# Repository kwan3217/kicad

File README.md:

# kicad
KiCad versions of my circuits

Many of my boards have the Open Source Hardware logo on them. Using this logo
requires having an open source license and publishing the source. In order to
support this, I have the URL of this repository engraved onto the boards themselves.

I have made a release for the Wearable Pocketometer boards, and intend to make a release
each time I have a board made.

All boards which have been released since September 2020 have enough information
to construct a bill of materials. This is in the form of Digikey part numbers attached
to each part in the KiCad .sch files.

Featured projects:

* Wearable Pocketometer -- IMU/GPS recording device designed to be worn by a roller-coaster passenger. 
It has a component that goes on your shoulder or hat, one in your pocket, and one in your shoe.

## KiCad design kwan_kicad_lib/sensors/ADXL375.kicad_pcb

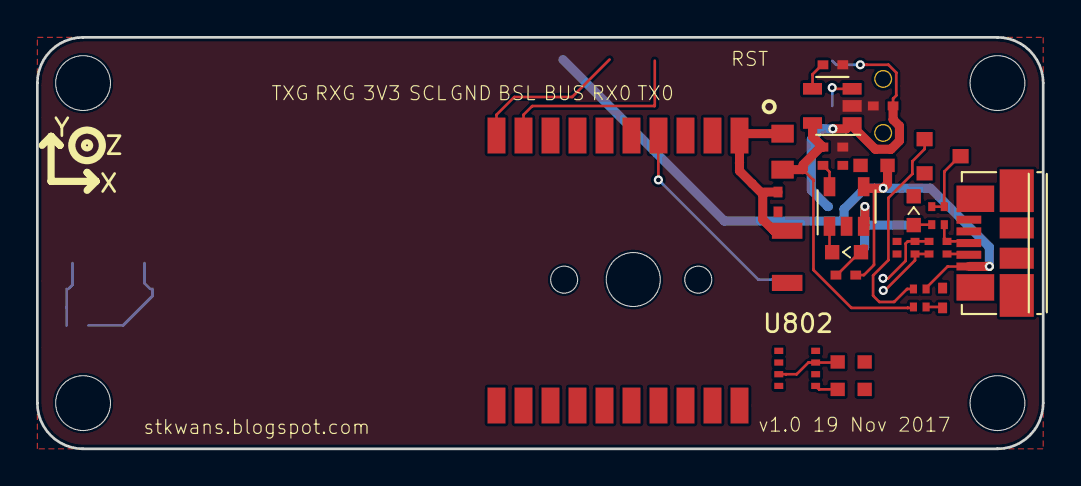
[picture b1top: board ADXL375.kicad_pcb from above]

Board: 2 copper layers, 55.9 x 22.9 mm, 39 parts (0 on the bottom side), 25 nets.

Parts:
B504: Coin_Cell; CR1220-2
C401, C405, C501, C714: 100nF; SMD_0402
C406, C704: 1uF; SMD_0402
C503: 10uF; SMD_1206
C623: 22pF; R_Array_Convex_2x0402
C715: 4.7nF; SMD_0402
C802, C803: 4.7uF; SMD_0603
C806, C808: 100nF; SMD_0603
D650: BLUE; D_0603
D801: YELLOW; D_0603
D802: DCC; SOT-23
J601: USB_MICROB; USB_Micro-B_Molex_47346-0001
J801: JST 2mm; SPARKFUN_JST_POWER
JP1, JP2, JP4, JP5: STAND-OFFTIGHT; STAND-OFF-TIGHT
L501: Ferrite; SMD_0805
Q650: PMOS; SOT-23
R406: 100; SMD_0402
R611: 22k; SMD_0402
R623: 33; R_Array_Convex_2x0402
R650: 1.5k; R_Array_Convex_2x0402
R651: 10k; R_Array_Convex_2x0402
R801: 10k; SMD_0402
R804: 1.5k; SMD_0402
S701: SPDT; SWITCH_DPDT_AZY0202
U401: ADXL375
U501: FGPMMOPA6H
U599: FGPMMOPA6H; Axis
U701: 3.3V; SOT-23-5
U801: MCP73831; SOT-23-5
U802: BME280

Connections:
/CONNECT: Q650.1, R651.4
/CONN_D+: J601.3, R623.4, R650.4
/CONN_D-: J601.2, R623.3
/D+: C623.2, R623.1
/D-: C623.1, R623.2
/GND: B504.-, C401.2, C405.2, C406.2, C501.1, C503.1, C623.3, C623.4, C802.2, C803.2, C806.1, C808.1, D650.1, J601.5, J601.6, J801.-, R611.1, R801.1, U401.2, U401.4, U401.5, U401.12, U501.3, U501.8, U501.12, U501.19, U801.2, U802.1, U802.5, U802.7
/ON: R611.2, R651.2
/PROG: R801.2, U801.5
/Regulator/BYP: C714.1, U701.4
/Regulator/PWR_EN: S701.2, U701.3
/SCL: U401.14, U802.4
/SDA: U401.13, U802.3
/STAT+: D801.2, R804.2
/STAT-: D801.1, U801.1
/USB_LIGHT+: Q650.3, R650.1, R650.2
/USB_LIGHT-: D650.2, R650.3
/VBACKUP: B504.+, U501.4
/VBUS: C802.1, D802.1, J601.1, R651.3, R804.1, U801.4
/VCC: C401.1, C806.2, C808.2, R406.1, U401.1, U401.7, U802.2, U802.6, U802.8
/VGPS: C501.2, C503.2, L501.2, U501.1
/VLIPO: C803.1, D802.2, J801.+, U801.3
/VRAW: C704.1, D802.3, S701.1, U701.1
/VS: C405.1, C406.1, R406.2, U401.6
GND: C704.2, C714.2, C715.2, S701.3, U701.2
VCC: C715.1, L501.1, R651.1, U701.5

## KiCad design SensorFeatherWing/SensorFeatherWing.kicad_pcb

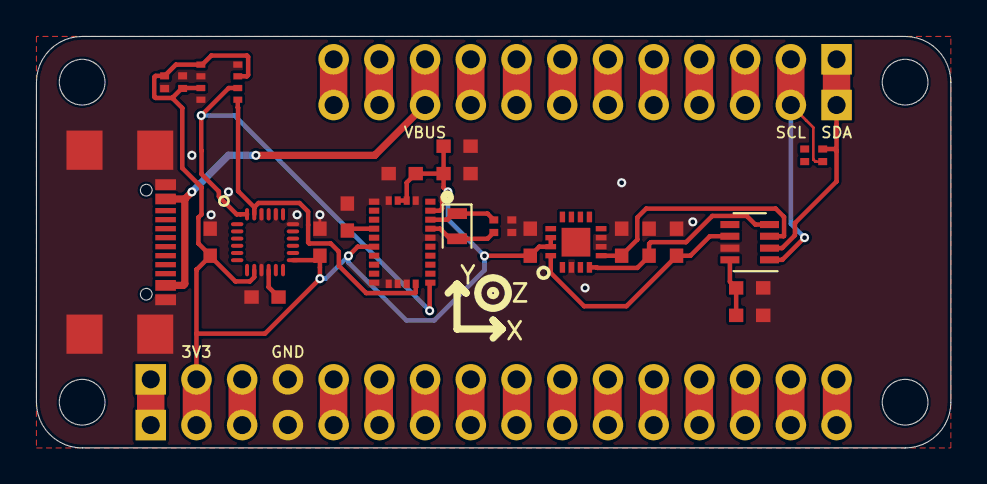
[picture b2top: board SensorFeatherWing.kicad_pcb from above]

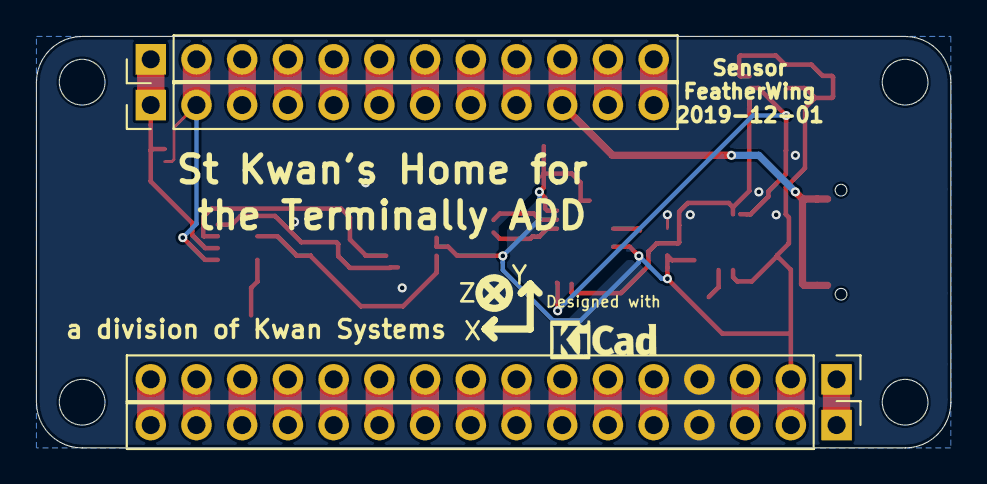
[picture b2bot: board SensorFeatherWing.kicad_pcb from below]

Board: 2 copper layers, 50.8 x 22.9 mm, 32 parts (4 on the bottom side), 35 nets.

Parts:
C208, C210, C213, C401, C402, C403, C607, C703, C709: 100nF; SMD_0603
C306: 100nF; R_Array_Convex_2x0402
C505: 4.7uF; SMD_0603
C608: 10uF; SMD_0603
C725: 120nF; SMD_0603
C726: 22pF; R_Array_Convex_2x0402
C728: 6.8nF; SMD_0603
J101, J102, J105, J106: STANDOFF; STANDOFF_FEATHER
J103, J107: Conn_01x16_Male; PinHeader_1x16_P2.54mm_Vertical
J104, J108: Conn_01x12_Male; PinHeader_1x12_P2.54mm_Vertical
J109: USB_C_Receptacle_USB2.0; USB4110
R101: 10k; R_Array_Convex_2x0402
U201: MPU9250; QFN24_PAD
U301: BME280
U501: MPU9250; Axis
U501#2: ADXL377
U601: AD7991; SOT-23-8
U701: BNO055
Y701: 32kiHz; Crystal_SMD_2012-2Pin_2.0x1.2mm

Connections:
+3V3: C208.2, C213.2, C306.1, C306.3, C505.1, C607.1, C608.1, C703.2, C725.1, C728.1, J103.2, J107.2, R101.1, R101.2, U201.8, U201.13, U301.2, U301.6, U301.8, U501#2.14, U501#2.15, U601.8, U701.3, U701.4, U701.11, U701.28
/BNO055/CAP: C709.1, U701.9
/BNO055/XIN32: C726.1, U701.27, Y701.1
/BNO055/XOUT32: C726.2, U701.26, Y701.2
/HighAcc/XACC: C403.2, U501#2.5, U601.3
/HighAcc/YACC: C402.2, U501#2.4, U601.4
/HighAcc/ZACC: C401.2, U501#2.16, U601.6
/MPU9250/REGOUT: C210.2, U201.10
/SCL: J104.2, J108.2, R101.3, U201.23, U301.4, U601.1, U701.19
/SDA: J104.1, J108.1, R101.4, U201.24, U301.3, U601.2, U701.20
GND: C208.1, C210.1, C213.1, C306.2, C306.4, C401.1, C402.1, C403.1, C505.2, C607.2, C608.2, C703.1, C709.2, C725.2, C726.3, C726.4, C728.2, J103.4, J107.4, J109.A1, J109.A12, J109.B1, J109.B12, J109.S1, U201.9, U201.18, U201.20, U201.22, U301.1, U301.5, U301.7, U501#2.2, U501#2.6, U501#2.7, U601.7, U701.2, U701.5, U701.6, U701.15, U701.16, U701.17, U701.18, U701.25
unnamed: J103.1, J107.1
unnamed: J103.3, J107.3
unnamed: J103.5, J107.5
unnamed: J103.6, J107.6
unnamed: J103.7, J107.7
unnamed: J103.8, J107.8
unnamed: J103.9, J107.9
unnamed: J103.10, J107.10
unnamed: J103.11, J107.11
unnamed: J103.12, J107.12
unnamed: J103.13, J107.13
unnamed: J103.14, J107.14
unnamed: J103.15, J107.15
unnamed: J103.16, J107.16
unnamed: J104.3, J108.3
unnamed: J104.4, J108.4
unnamed: J104.5, J108.5
unnamed: J104.6, J108.6
unnamed: J104.7, J108.7
unnamed: J104.8, J108.8
unnamed: J104.9, J108.9
unnamed: J104.11, J108.11
unnamed: J104.12, J108.12
VBUS: J104.10, J108.10, J109.A4, J109.A9, J109.B4, J109.B9

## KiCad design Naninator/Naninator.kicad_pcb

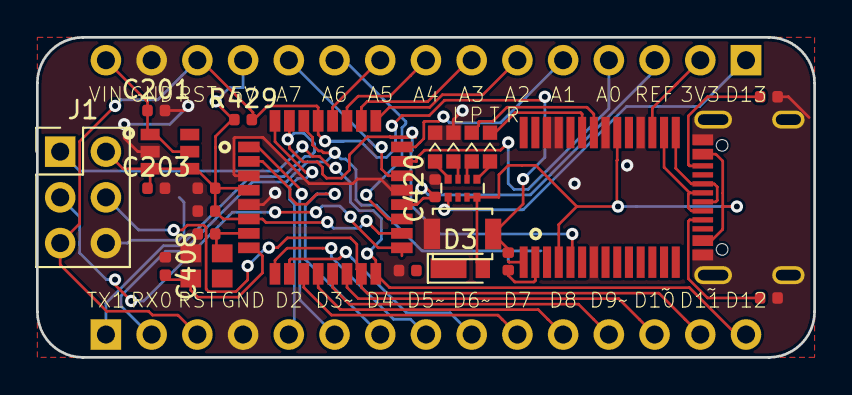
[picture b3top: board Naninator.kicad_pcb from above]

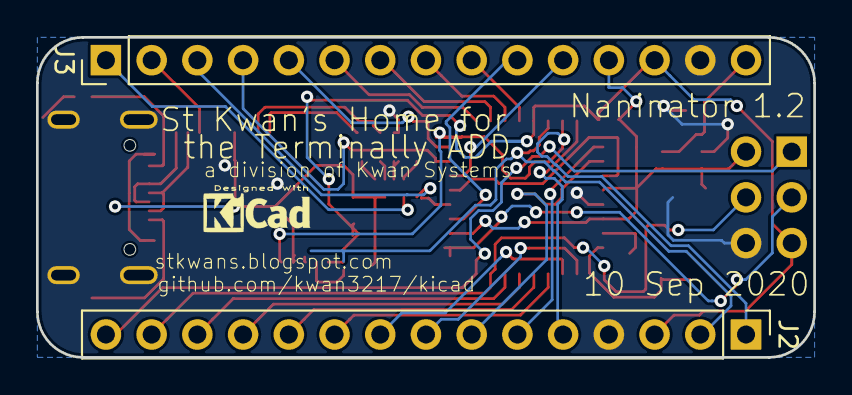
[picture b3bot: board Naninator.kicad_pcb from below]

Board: 2 copper layers, 43.2 x 17.8 mm, 29 parts (4 on the bottom side), 42 nets.

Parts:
C201: 1uF; C_0402_1005Metric
C203: 4.7uF; C_0402_1005Metric
C302, C404, C406, C418, C420: 100nF; C_0402_1005Metric
C407, C408: 22pF; C_0402_1005Metric
D3: MSSP12L; D_TUMD2
D322: BLUE; D_0603
D323: RED; D_0603
D401: GREEN; D_0603
D402: YELLOW; D_0603
G101: Designed With; Symbol_KiCAD-Logo_CopperAndSilkScreenTop_small
G102: KwanSystems; StKwansSoldermask
J1: CONN_02X03; PinHeader_2x03_P2.54mm_Vertical
J2, J3: CONN_01X15; PinHeader_1x15_P2.54mm_Vertical
J401: USB_C_Receptacle_USB2.0; GCTUSBTypeC_PTH
R201: 680; R_Array_Convex_4x0402
R401, R402: 5.1k; R_0402_1005Metric
R429: 10k; R_0402_1005Metric
S429: SW_SPST; SW_SPST_B3U-1000P
U201: MAX8881 5V; SOT-23-6
U301: FT232RL; SSOP-28_5.3x10.2mm_Pitch0.65mm
U401: ATMEGA328P-AU; LQFP-32_7x7mm_Pitch0.8mm
Y407: 16MHz; Crystal_SMD_2520-4pin_2.5x2.0mm

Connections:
+3V3: J3.2, U301.17
/A0: J3.4, U401.23
/A1: J3.5, U401.24
/A2: J3.6, U401.25
/A3: J3.7, U401.26
/A4: J3.8, U401.27
/A5: J3.9, U401.28
/A6: J3.10, U401.19
/A7: J3.11, U401.22
/AREF: C420.1, J3.3, U401.20
/ATmega/XTAL1: C407.2, U401.7, Y407.1
/ATmega/XTAL2: C408.2, U401.8, Y407.3
/D0/RX: J2.2, U301.1, U401.30
/D1/TX: J2.1, U301.5, U401.31
/D2: J2.5, U401.32
/D3: J2.6, U401.1
/D4: J2.7, U401.2
/D5: J2.8, U401.9
/D6: J2.9, U401.10
/D7: J2.10, U401.11
/D8: J2.11, U401.12
/D9: J2.12, U401.13
/D10: J2.13, U401.14
/D11: J1.4, J2.14, U401.15
/D12: J1.1, J2.15, U401.16
/D13: J1.3, J3.1, R201.5, U401.17
/D13-: D402.2, R201.4
/PWR_LED-: D401.2, R201.3
/USB Serial/D+: J401.A6, J401.B6, U301.15
/USB Serial/D-: J401.A7, J401.B7, U301.16
/USB Serial/DTR: C302.1, U301.2
/USB Serial/RX_LED+: D323.2, R201.1
/USB Serial/RX_LED-: D323.1, U301.23
/USB Serial/TX_LED+: D322.2, R201.2
/USB Serial/TX_LED-: D322.1, U301.22
/USB Serial/USB-C Connector/CC1: J401.A5, R401.1
/USB Serial/USB-C Connector/CC2: J401.B5, R402.1
/VBUS: D3.2, J401.A4, J401.A9, J401.B4, J401.B9, R201.7, R201.8, U301.4, U301.20
/~RESET: C302.2, J1.5, J2.3, J3.13, R429.2, S429.1, U401.29
GND: C201.2, C203.2, C404.2, C406.2, C407.1, C408.1, C418.2, C420.2, D401.1, D402.1, J1.6, J2.4, J3.14, J401.A1, J401.A12, J401.B1, J401.B12, J401.S1, R401.2, R402.2, S429.2, U201.2, U301.7, U301.18, U301.21, U301.25, U301.26, U401.3, U401.5, U401.21, Y407.2
HT: C201.1, J3.15, U201.1, U201.5
VCC: C203.1, C404.1, C406.1, C418.1, D3.1, J1.2, J3.12, R201.6, R429.1, U201.3, U201.4, U401.4, U401.6, U401.18

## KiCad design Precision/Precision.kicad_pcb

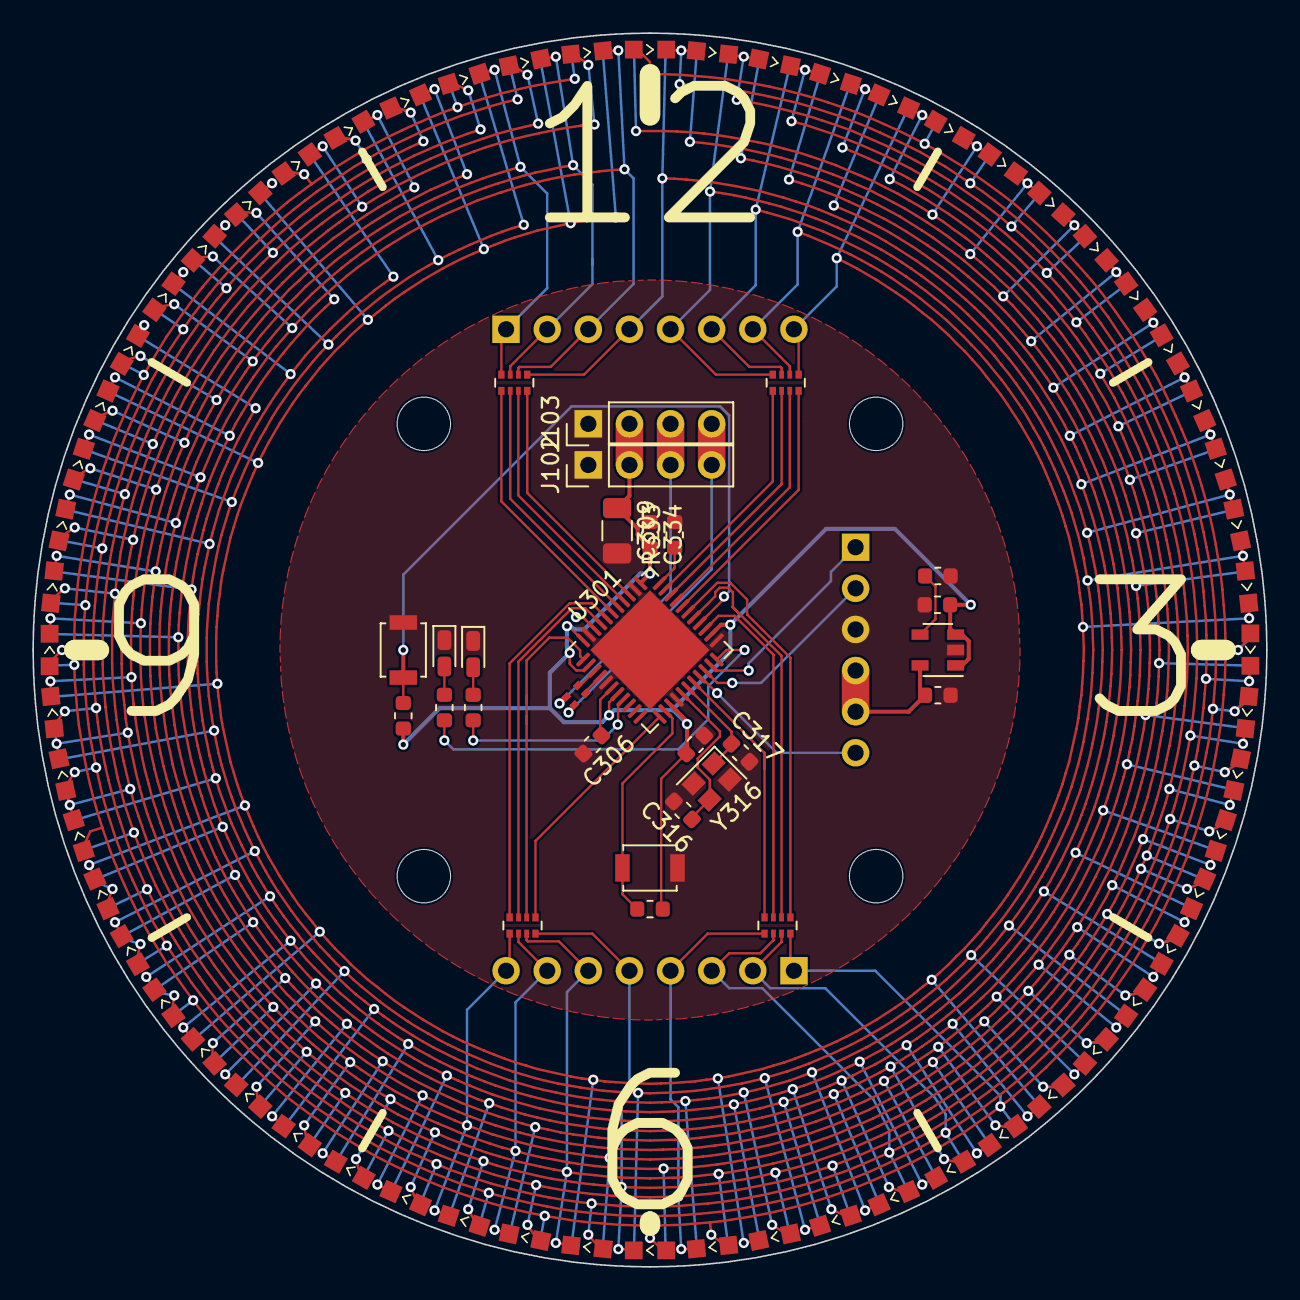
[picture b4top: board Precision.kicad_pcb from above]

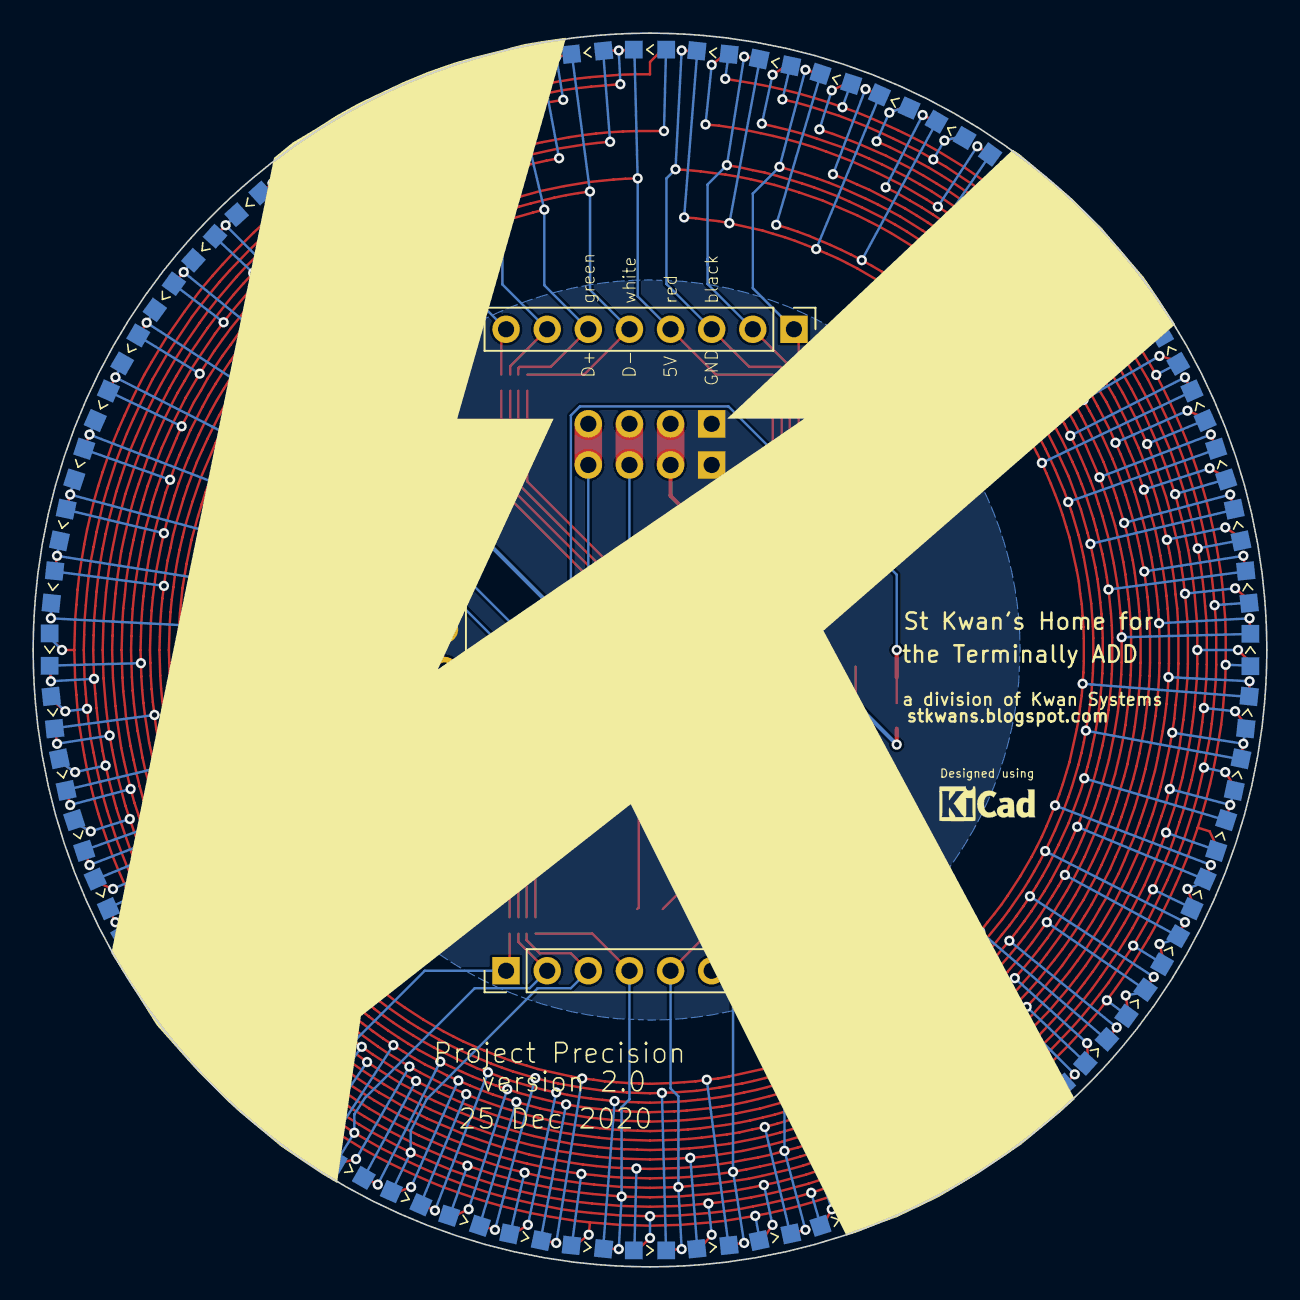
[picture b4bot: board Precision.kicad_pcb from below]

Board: 2 copper layers, 76.2 x 76.2 mm, 157 parts (65 on the bottom side), 53 nets.

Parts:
C306, C401: 1uF; C_0603_1608Metric
C309: 10uF; C_1206_3216Metric
C314, C334, C404: 100nF; C_0603_1608Metric
C316, C317: 22pF; C_0603_1608Metric
C405: 2.2uF; C_0603_1608Metric
D000, D001, D002, D003, D004, D005, D006, D007, D008, D009, D010, D011, D012, D013, D014, D015, D016, D017, D018, D019, D020, D021, D022, D023, D024, D025, D026, D027, D028, D029, D030, D031, D032, D033, D034, D035, D036, D037, D038, D039, D040, D041, D042, D043, D044, D045, D046, D047, D048, D049, D050, D051, D052, D053, D054, D055, D056, D057, D058, D059: HOUR; D_0603_SIDE
D100, D101, D102, D103, D104, D105, D106, D107, D108, D109, D110, D111, D112, D113, D114, D115, D116, D117, D118, D119, D120, D121, D122, D123, D124, D125, D126, D127, D128, D129, D130, D131, D132, D133, D134, D135, D136, D137, D138, D139, D140, D141, D142, D143, D144, D145, D146, D147, D148, D149, D150, D151, D152, D153, D154, D155, D156, D157, D158, D159: MIN; D_0603_SIDE
D308: RED; LED_0603_1608Metric_Castellated
D322: green; LED_0603_1608Metric_Castellated
G101: KwanSystems; PrecisionKwan
G102: DesignedWithKicad; Symbol_KiCAD-Logo_CopperAndSilkScreenTop_small
J101: M06PTH; PinHeader_1x06_P2.54mm_Vertical
J102, J103: M04PTH; PinHeader_1x04_P2.54mm_Vertical
J104, J105: Conn_01x08; PinHeader_1x08_P2.54mm_Vertical
JP101: STANDOFF; STANDOFF_NONPLATED
JP102, JP103, JP104: STAND-OFF; STANDOFF_NONPLATED
R101, R313, R333: 10k; R_0603_1608Metric
R102, R103, R104, R105: 47; R_Array_Convex_4x0402
R303: 22; R_Array_Convex_2x0402
R308, R322: 1k; R_0603_1608Metric
S102: B3U-1000P; SW_SPST_B3U-1000P
S313: RESET; SW_SPST_B3U-1000P
U301: ATmega32U4-MU; QFN-44-1EP_7x7mm_P0.5mm_EP5.2x5.2mm
U401: MIC5319 3.3V; SOT-23-5
Y316: 16MHz; Crystal_SMD_2520-4Pin_2.5x2.0mm

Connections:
+3V3: C405.1, J101.4, J101.5, U401.5
/3.3V Regulator/BYP: C404.1, U401.4
/Arduino 32U4/HWB: R333.1, U301.33
/Arduino 32U4/RD+: R303.1, U301.4
/Arduino 32U4/RD-: R303.2, U301.3
/Arduino 32U4/RESET: R313.2, S313.1, U301.13
/Arduino 32U4/RXLED-: D308.2, R308.2
/Arduino 32U4/RXLED_SS: R308.1, U301.8
/Arduino 32U4/TXLED: R322.1, U301.22
/Arduino 32U4/TXLED-: D322.2, R322.2
/Arduino 32U4/UCAP: C306.1, U301.6
/Arduino 32U4/XTAL1: C317.1, U301.17, Y316.1
/Arduino 32U4/XTAL2: C316.1, U301.16, Y316.3
/D+: J102.4, J103.4, R303.4
/D-: J102.3, J103.3, R303.3
/GPS_RX: J101.1, U301.21
/GPS_TX: J101.2, U301.20
/P01: R105.1, U301.28
/P02: R105.2, U301.27
/P03: R105.3, U301.25
/P04: R105.4, U301.18
/P05: R104.1, U301.12
/P06: R104.2, U301.1
/P07: R104.3, U301.41
/P08: R104.4, U301.40
/P09: R103.1, U301.39
/P10: R103.2, U301.38
/P11: R103.3, U301.37
/P12: R103.4, U301.36
/P13: R102.1, U301.32
/P14: R102.2, U301.31
/P15: R102.3, U301.30
/P16: R102.4, U301.29
/PPS: J101.6, U301.19
/Q01: D000.2, D015.2, D029.2, D042.2, D054.2, D105.2, D115.2, D124.2, D132.2, D139.2, D145.2, D150.2, D154.2, D157.2, D159.2, J105.1, R105.8
/Q02: D000.1, D001.2, D016.2, D030.2, D043.2, D055.2, D106.2, D116.2, D125.2, D133.2, D140.2, D146.2, D151.2, D155.2, D158.2, J105.2, R105.7
/Q03: D001.1, D002.2, D015.1, D017.2, D031.2, D044.2, D056.2, D107.2, D117.2, D126.2, D134.2, D141.2, D147.2, D152.2, D156.2, J105.3, R105.6
/Q04: D002.1, D003.2, D016.1, D018.2, D029.1, D032.2, D045.2, D057.2, D108.2, D118.2, D127.2, D135.2, D142.2, D148.2, D153.2, J105.4, R105.5
/Q05: D003.1, D004.2, D017.1, D019.2, D030.1, D033.2, D042.1, D046.2, D058.2, D109.2, D119.2, D128.2, D136.2, D143.2, D149.2, J105.5, R104.8
/Q06: D004.1, D005.2, D018.1, D020.2, D031.1, D034.2, D043.1, D047.2, D054.1, D059.2, D110.2, D120.2, D129.2, D137.2, D144.2, J105.6, R104.7
/Q07: D005.1, D006.2, D019.1, D021.2, D032.1, D035.2, D044.1, D048.2, D055.1, D100.2, D105.1, D111.2, D121.2, D130.2, D138.2, J105.7, R104.6
/Q08: D006.1, D007.2, D020.1, D022.2, D033.1, D036.2, D045.1, D049.2, D056.1, D101.2, D106.1, D112.2, D115.1, D122.2, D131.2, J105.8, R104.5
/Q09: D007.1, D008.2, D021.1, D023.2, D034.1, D037.2, D046.1, D050.2, D057.1, D102.2, D107.1, D113.2, D116.1, D123.2, D124.1, J104.1, R103.8
/Q10: D008.1, D009.2, D022.1, D024.2, D035.1, D038.2, D047.1, D051.2, D058.1, D103.2, D108.1, D114.2, D117.1, D125.1, D132.1, J104.2, R103.7
/Q11: D009.1, D010.2, D023.1, D025.2, D036.1, D039.2, D048.1, D052.2, D059.1, D104.2, D109.1, D118.1, D126.1, D133.1, D139.1, J104.3, R103.6
/Q12: D010.1, D011.2, D024.1, D026.2, D037.1, D040.2, D049.1, D053.2, D100.1, D110.1, D119.1, D127.1, D134.1, D140.1, D145.1, J104.4, R103.5
/Q13: D011.1, D012.2, D025.1, D027.2, D038.1, D041.2, D050.1, D101.1, D111.1, D120.1, D128.1, D135.1, D141.1, D146.1, D150.1, J104.5, R102.8
/Q14: D012.1, D013.2, D026.1, D028.2, D039.1, D051.1, D102.1, D112.1, D121.1, D129.1, D136.1, D142.1, D147.1, D151.1, D154.1, J104.6, R102.7
/Q15: D013.1, D014.2, D027.1, D040.1, D052.1, D103.1, D113.1, D122.1, D130.1, D137.1, D143.1, D148.1, D152.1, D155.1, D157.1, J104.7, R102.6
/Q16: D014.1, D028.1, D041.1, D053.1, D104.1, D114.1, D123.1, D131.1, D138.1, D144.1, D149.1, D153.1, D156.1, D158.1, D159.1, J104.8, R102.5
/SET: R101.1, S102.1, U301.26
GND: C306.2, C309.2, C314.1, C316.2, C317.2, C334.1, C401.2, C404.2, C405.2, D308.1, D322.1, J101.3, J102.1, J103.1, R333.2, S102.2, S313.2, U301.5, U301.15, U301.23, U301.35, U301.43, U301.45, U401.2, Y316.2, Y316.4
VBUS: C309.1, C314.2, C334.2, C401.1, J102.2, J103.2, R101.2, R313.1, U301.2, U301.7, U301.14, U301.24, U301.34, U301.44, U401.1, U401.3

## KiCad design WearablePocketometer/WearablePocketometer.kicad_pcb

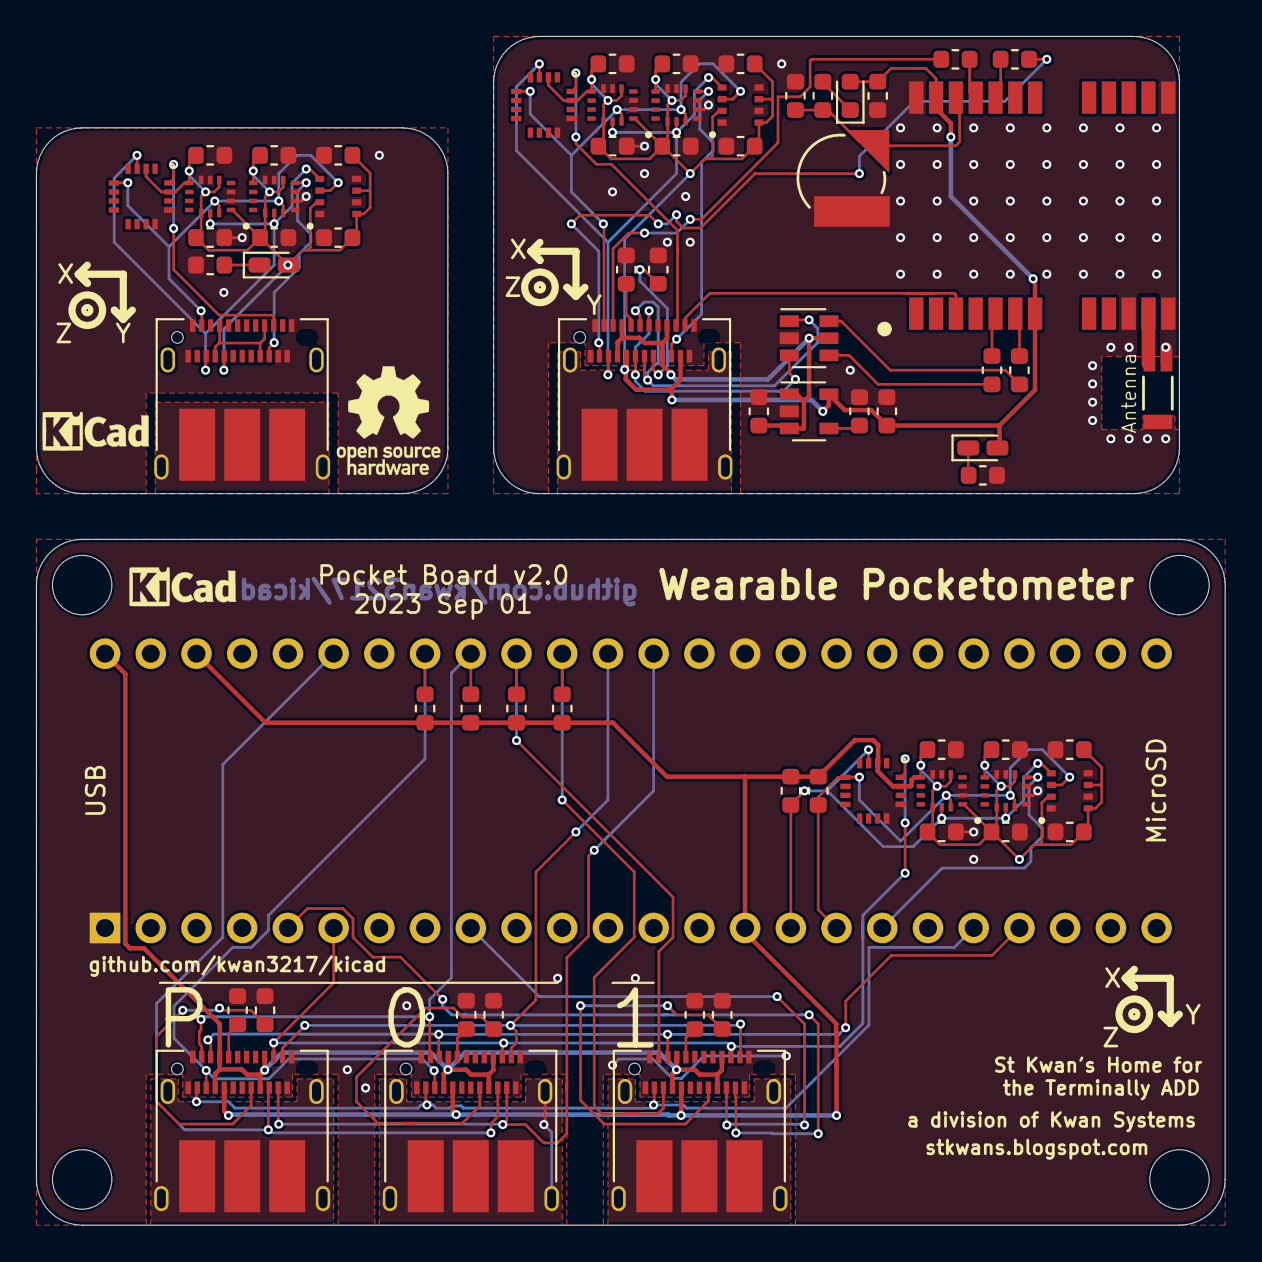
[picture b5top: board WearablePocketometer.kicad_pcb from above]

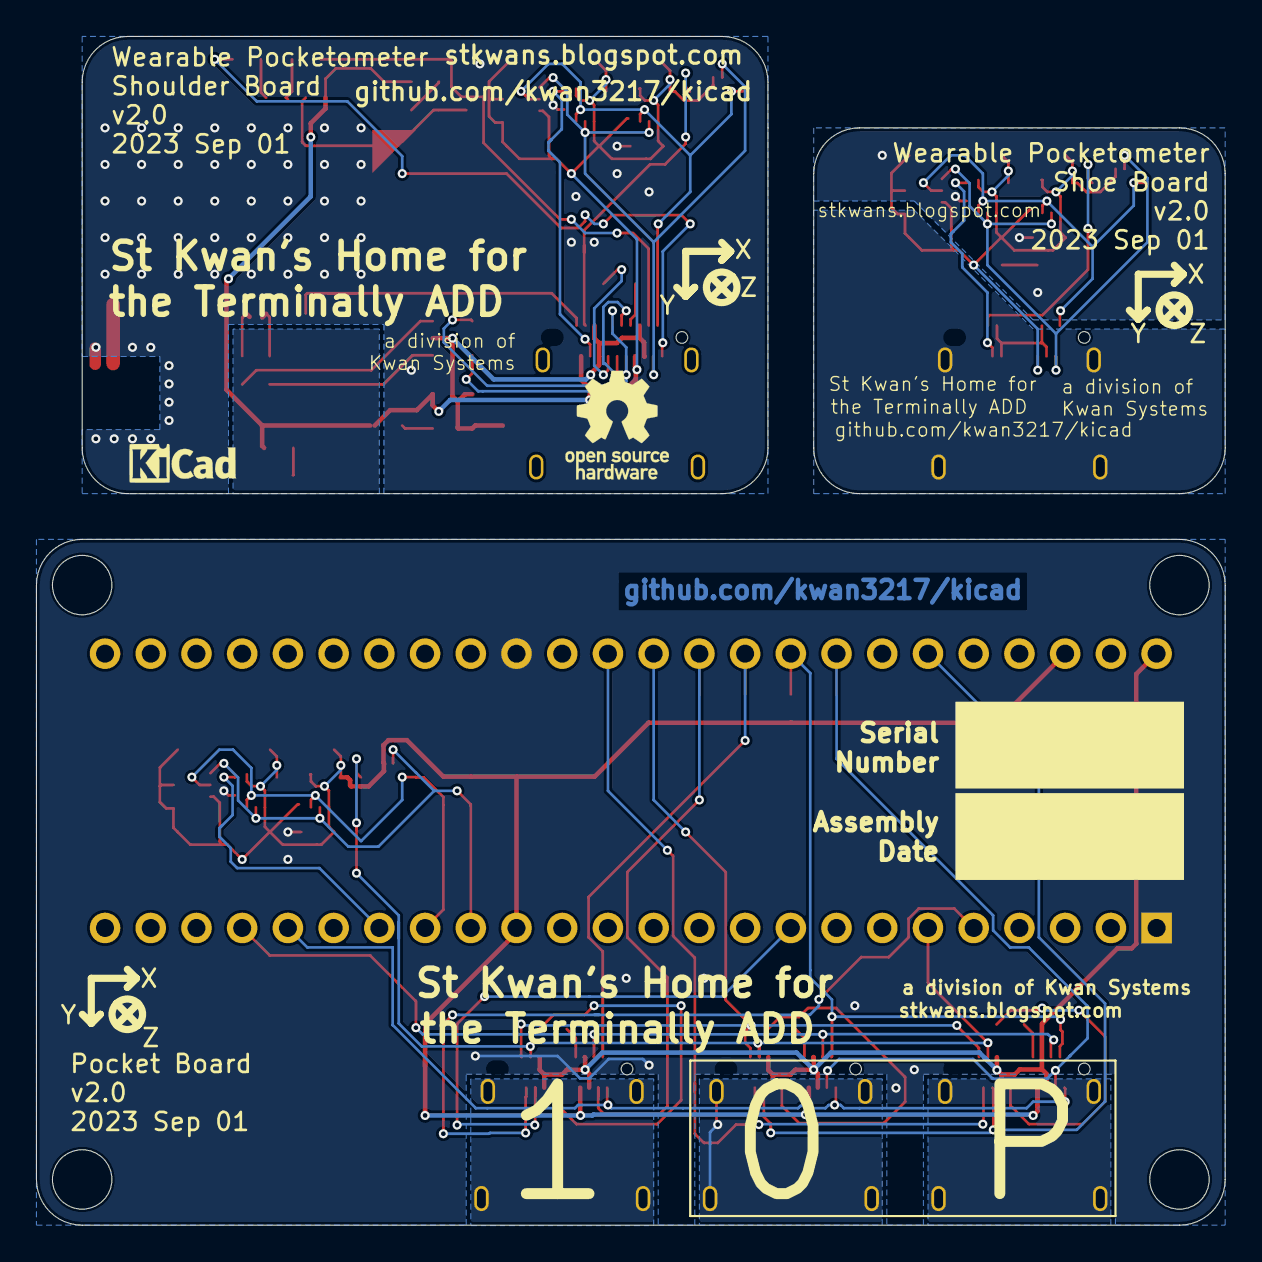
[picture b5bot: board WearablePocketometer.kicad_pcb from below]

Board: 2 copper layers, 66.0 x 66.0 mm, 87 parts (5 on the bottom side), 57 nets.

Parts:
B901: ML414H; Coin_Cell_ML414H
C201, C202, C301, C302, C401, C402, C601, C602, C701, C702, C801, C802, C1002, C1401, C1402, C1501, C1502, C1601, C1602: 100nF; C_0603_1608Metric
C901, C1001: 1uF; C_0603_1608Metric
C1003: 2.2uF; C_0603_1608Metric
D501, D1301: RED; LED_0603_1608Metric_Castellated
D901: 0.5A/40V/420mV; D_0603_1608Metric
G101, G501, G1301: DesignedWithKicad; Symbol_KiCAD-Logo_CopperAndSilkScreenTop_small
G102, G103, G502, G1302: KwanSystems; StKwansSoldermask
G104: OSHW; OSHW-Symbol_6.7x6mm_SolderMask
G105, G504, G1304: Axis
G503, G1303: OSHW; OSHW-Logo_5.7x6mm_SilkScreen
J101, J102, J103, J104: STANDOFF; STANDOFF_NONPLATED
J1101, J1201, J1701, J1801, J1901: USB_C_Receptacle; USB_C_Receptacle_Amphenol_12401610E4-2A
R101, R102, R103, R104, R105, R106, R501, R1301: 1k; R_0603_1608Metric
R901, R902, R905, R906: 27; R_0603_1608Metric
R903: 100k; R_0603_1608Metric
R904: 33; R_0603_1608Metric
R1101, R1102, R1201, R1202, R1701, R1702, R1901, R1902: 5.1k; R_0603_1608Metric
U101, U501, U1301: AK09970
U102: Teensy4.1; Teensy2x24
U201, U301, U601, U801, U1401, U1601: LSM6DSO; LGA-14L
U401, U701, U1501: BME280
U901: NEO_M8U; NEO-M9N_M8T_M8U
U1001: MIC5319 3.3V; SOT-23-5
U1201: USBLC6-2SC6; SOT-23-6
Y901: W3011

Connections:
+3V3: C201.1, C202.1, C301.1, C302.1, C401.1, C402.2, J1101.B8, J1701.B8, J1901.B8, R101.1, R102.1, R103.2, R104.2, R105.2, R106.2, U101.2, U101.15, U102.15, U102.46, U201.5, U201.8, U201.12, U301.1, U301.5, U301.8, U301.12, U401.2, U401.6, U401.8
+5V: J1101.A4, J1101.A9, J1101.B4, J1101.B9, J1701.A4, J1701.A9, J1701.B4, J1701.B9, J1901.A4, J1901.A9, J1901.B4, J1901.B9, U102.48
/MAG~RST: J1101.A10, J1701.A10, J1901.A10, U101.16, U102.6
/P0_ID: J1701.B2, J1901.B2, U102.36
/P0_INT: J1701.B3, J1901.B3, U102.43
/P0_SCL: J1701.B10, J1901.B10, R103.1, U102.41
/P0_SDA: J1701.A2, J1901.A2, R104.1, U102.40
/P1_ID: J1101.B2, U102.5
/P1_INT: J1101.B3, U102.9
/P1_SCL: J1101.B10, R106.1, U102.38
/P1_SDA: J1101.A2, R105.1, U102.39
/P2_INT: U102.18, U201.4
/P2_SCL: R102.2, U101.3, U102.16, U201.13, U301.13, U401.4
/P2_SDA: R101.2, U101.5, U102.17, U201.14, U301.14, U401.3
/PPS: J1101.A11, J1701.A11, J1901.A11, U102.37
/RX_GPS: J1101.A3, J1701.A3, J1901.A3, U102.21
/Shoe/Q_3V3: C1401.1, C1402.1, C1501.1, C1502.2, C1601.1, C1602.1, D1301.2, J1801.B8, U1301.2, U1301.15, U1401.5, U1401.8, U1401.12, U1501.2, U1501.6, U1501.8, U1601.1, U1601.5, U1601.8, U1601.12
/Shoe/Q_GND: C1401.2, C1402.2, C1501.2, C1502.1, C1601.2, C1602.2, J1801.A1, J1801.A12, J1801.B1, J1801.B2, J1801.B12, R1301.2, U1301.12, U1301.13, U1401.1, U1401.2, U1401.3, U1401.6, U1401.7, U1501.1, U1501.5, U1501.7, U1601.2, U1601.3, U1601.6, U1601.7
/Shoe/Q_INT: J1801.B3, U1401.4
/Shoe/Q_MAG~RST: J1801.A10, U1301.16
/Shoe/Q_SCL: J1801.B10, U1301.3, U1401.13, U1501.4, U1601.13
/Shoe/Q_SDA: J1801.A2, U1301.5, U1401.14, U1501.3, U1601.14
/Shoe/Shoe Downstream/VBUS: J1801.A4, J1801.A9, J1801.B4, J1801.B9
/Shoe/Shoe Upstream/CC1: J1701.A5, R1701.1
/Shoe/Shoe Upstream/CC2: J1701.B5, R1702.1
/Shoulder/D+: R902.1, U1201.6
/Shoulder/D-: R901.1, U1201.4
/Shoulder/GPS/GPS_ANT1: U901.11, Y901.1
/Shoulder/GPS/R_D+: R902.2, U901.6
/Shoulder/GPS/R_D-: R901.2, U901.5
/Shoulder/GPS/V_BATT: B901.1, C901.1, R904.2, U901.22
/Shoulder/Q_3V3: C601.1, C602.1, C701.1, C702.2, C801.1, C802.1, C1003.1, D501.2, D901.2, J1201.B2, J1201.B8, R903.1, U501.2, U501.15, U601.5, U601.8, U601.12, U701.2, U701.6, U701.8, U801.1, U801.5, U801.8, U801.12, U901.7, U901.23, U1001.5
/Shoulder/Q_5V: C1001.1, J1201.A4, J1201.A9, J1201.B4, J1201.B9, U1001.1, U1001.3, U1201.5
/Shoulder/Q_GND: B901.2, C601.2, C602.2, C701.2, C702.1, C801.2, C802.2, C901.2, C1001.2, C1002.2, C1003.2, J1201.A1, J1201.A12, J1201.B1, J1201.B12, R501.2, R903.2, R1201.2, R1202.2, U501.12, U501.13, U601.1, U601.2, U601.3, U601.6, U601.7, U701.1, U701.5, U701.7, U801.2, U801.3, U801.6, U801.7, U901.10, U901.12, U901.13, U901.24, U1001.2, U1201.2, Y901.2, Y901.3
/Shoulder/Q_INT: J1201.B3, U601.4
/Shoulder/Q_MAG~RST: J1201.A10, U501.16
/Shoulder/Q_PPS: J1201.A11, U901.3
/Shoulder/Q_RX_GPS: J1201.A3, R905.2
/Shoulder/Q_SCL: J1201.B10, U501.3, U601.13, U701.4, U801.13
/Shoulder/Q_SDA: J1201.A2, U501.5, U601.14, U701.3, U801.14
/Shoulder/Q_TX_GPS: J1201.B11, R906.2
/Shoulder/Regulator/BYP: C1002.1, U1001.4
/Shoulder/Shoulder Downstream/CC1: J1201.A5, R1201.1
/Shoulder/Shoulder Downstream/CC2: J1201.B5, R1202.1
/Shoulder/Shoulder Downstream/PD+: J1201.A6, J1201.B6, U1201.1
/Shoulder/Shoulder Downstream/PD-: J1201.A7, J1201.B7, U1201.3
/Shoulder/Shoulder Upstream/CC1: J1101.A5, R1101.1
/Shoulder/Shoulder Upstream/CC2: J1101.B5, R1102.1
/TX_GPS: J1101.B11, J1701.B11, J1901.B11, U102.20
/USB C Power/CC1: J1901.A5, R1901.1
/USB C Power/CC2: J1901.B5, R1902.1
GND: C201.2, C202.2, C301.2, C302.2, C401.2, C402.1, J1101.A1, J1101.A12, J1101.B1, J1101.B12, J1701.A1, J1701.A12, J1701.B1, J1701.B12, J1901.A1, J1901.A12, J1901.B1, J1901.B12, R1101.2, R1102.2, R1701.2, R1702.2, R1901.2, R1902.2, U101.12, U101.13, U102.1, U102.34, U201.1, U201.2, U201.3, U201.6, U201.7, U301.2, U301.3, U301.6, U301.7, U401.1, U401.5, U401.7
unnamed: D501.1, R501.1
unnamed: D901.1, R904.1
unnamed: D1301.1, R1301.1
unnamed: R905.1, U901.21
unnamed: R906.1, U901.20

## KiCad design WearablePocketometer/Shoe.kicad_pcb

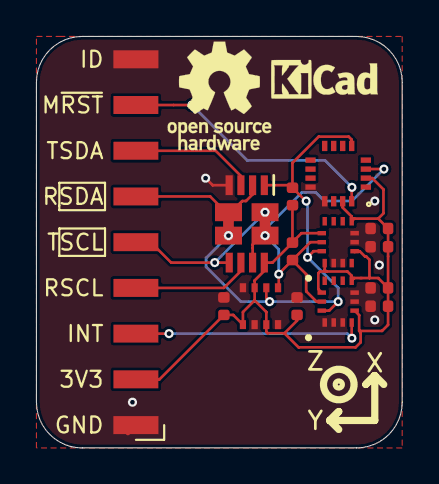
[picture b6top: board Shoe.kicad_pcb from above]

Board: 2 copper layers, 20.3 x 22.9 mm, 20 parts (1 on the bottom side), 10 nets.

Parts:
C1305, C1308, C1406, C1408, C1505, C1508: 100nF; C_0402_1005Metric
G501: DesignedWithKicad; Symbol_KiCAD-Logo_CopperAndSilkScreenTop_small
G502: KwanSystems; StKwansSoldermask
G503: OSHW; OSHW-Logo_5.7x6mm_SilkScreen
G904: Axis
J1201: Conn_01x09_Male; Harwin_M20-89009xx_1x09_P2.54mm_Horizontal
J1202, J1207: SolderJumper_2_Bridged; SolderJumper-2_Bridged
R1201, R1207: 10k; R_0402_1005Metric
U1201: AK09970
U1202: P82B96; TSSOP-8_3x3mm_P0.65mm
U1301, U1501: LSM6DSO; LGA-14L
U1401: BME280

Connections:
/Shoe/Q_3V3: C1305.1, C1308.1, C1406.1, C1408.2, C1505.1, C1508.1, J1201.2, R1201.1, R1207.1, U1201.2, U1201.15, U1202.8, U1301.5, U1301.8, U1301.12, U1401.2, U1401.6, U1401.8, U1501.1, U1501.5, U1501.8, U1501.12
/Shoe/Q_GND: C1305.2, C1308.2, C1406.2, C1408.1, C1505.2, C1508.2, J1201.1, J1201.9, U1201.12, U1201.13, U1202.4, U1301.1, U1301.2, U1301.3, U1301.6, U1301.7, U1401.1, U1401.5, U1401.7, U1501.2, U1501.3, U1501.6, U1501.7
/Shoe/Q_INT: J1201.3, U1301.4
/Shoe/Q_MAG~RST: J1201.8, U1201.16
/Shoe/Q_RX_SCL: J1201.4, U1202.6
/Shoe/Q_RX_SDA: J1201.6, J1202.2, U1202.2
/Shoe/Q_TX_SCL: J1201.5, J1207.2, U1202.5
/Shoe/Q_TX_SDA: J1201.7, U1202.3
/Shoe/SCL: J1207.1, R1207.2, U1201.3, U1202.7, U1301.13, U1401.4, U1501.13
/Shoe/SDA: J1202.1, R1201.2, U1201.5, U1202.1, U1301.14, U1401.3, U1501.14
